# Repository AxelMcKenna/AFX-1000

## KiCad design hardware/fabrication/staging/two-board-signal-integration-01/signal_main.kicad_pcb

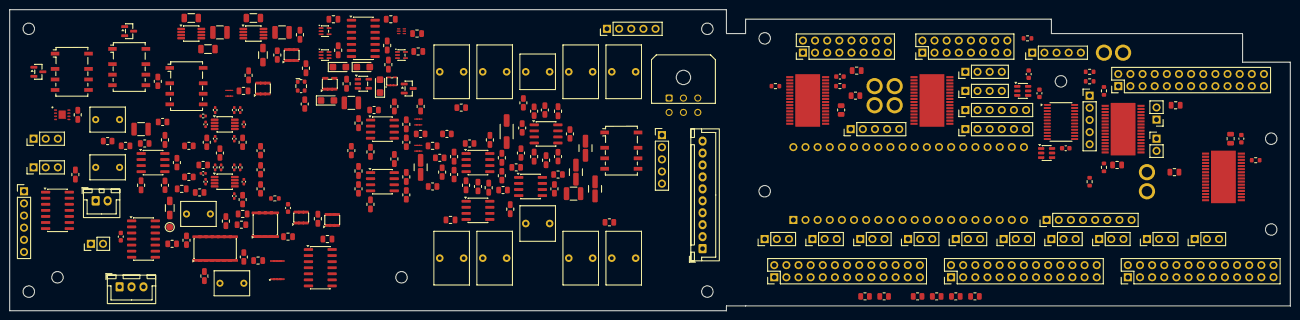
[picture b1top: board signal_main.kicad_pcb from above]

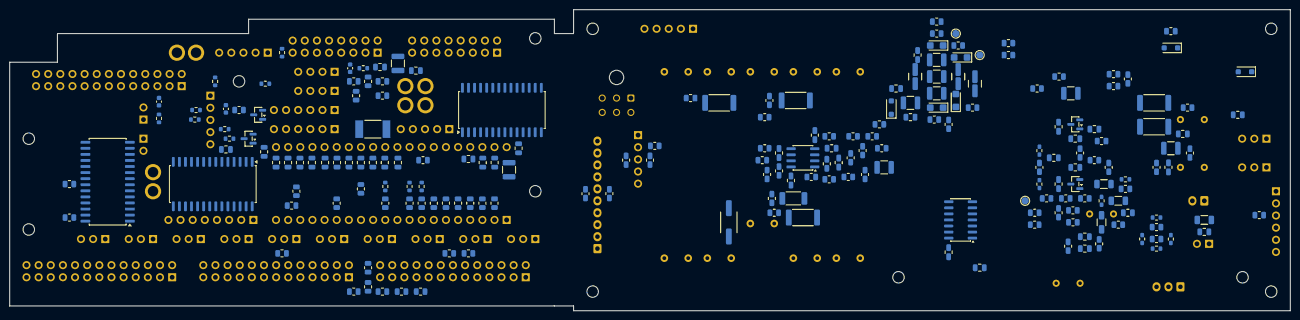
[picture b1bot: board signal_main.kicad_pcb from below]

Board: 8 copper layers, 268.0 x 63.0 mm, 477 parts (202 on the bottom side), 384 nets, no tracks yet.

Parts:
A_C101, A_C102, A_C115, A_C116: 1pF C0G +/-0.1pF; C_0402_1005Metric
A_C103, A_C117: 47pF C0G 5%; C_0805_2012Metric
A_C104, A_C105, A_C118, A_C119: 22pF C0G 5%; C_0805_2012Metric
A_C106, A_C120: 100nF 25V X7R; C_0805_2012Metric
A_C107, A_C121: 1uF 63V film 10%; C_Rect_L7.2mm_W5.0mm_P5.00mm
A_C108, A_C122: 10uF 16V X7R; C_1206_3216Metric
A_C109, A_C123: 47uF 25V X7S; C_1210_3225Metric
A_C110, A_C111, A_C124, A_C125: 47uF 6.3V X7S; C_1206_3216Metric
A_C112, A_C126: 2.2uF 16V X7R; C_0805_2012Metric
A_C113, A_C114, A_C127, A_C128: 100nF 16V X7R; C_0402_1005Metric
A_C129, A_C130, A_C131, A_C132, A_C220, A_C221, A_C222, A_C223, A_C224, A_C225, A_C226, A_C228, A_C229, A_C311, A_C312, A_C313, A_C314, A_C315, A_C316, A_C317, A_C318, A_C323, A_C324, A_C405, A_C406, A_C505, A_C506, A_C507, A_C508: 100nF 50V X7R; C_0805_2012Metric
A_C133, A_C134: 10uF 50V X7R; C_1206_3216Metric
A_C135, A_C136: 100nF 16V X7R; C_0603_1608Metric
A_C201, A_C202, A_C205: 1uF 10V X7R 10%; C_0805_2012Metric
A_C203, A_C210, A_C212, A_C214: 100nF 50V C0G 5%; C_1210_3225Metric
A_C204, A_C206, A_C207, A_C208, A_C209, A_C211, A_C213, A_C215: 1uF 10V tantalum 10%; CP_EIA-3216-18_Kemet-A
A_C216, A_C218, A_C227: 2.2uF 25V X7R 10%; C_1210_3225Metric
A_C217, A_C219: 10uF 16V X7R 10%; C_1210_3225Metric
A_C230, A_C231, A_C232, A_C610, A_C611, A_C612: 100nF 16V X7R; C_0805_2012Metric
A_C301, A_C302, A_C306, A_C307: 510pF 50V C0G 2%; C_0805_2012Metric
A_C303, A_C308: 51pF 50V C0G 2%; C_0805_2012Metric
A_C304, A_C305, A_C309, A_C310: 1nF 50V C0G 1%; C_0805_2012Metric
A_C319, A_C320, A_C509, A_C510, A_C511, A_C512: 10uF 50V X7R; C_1210_3225Metric
A_C321, A_C322: 2.2uF film 63V 10%; C_Rect_L7.2mm_W7.2mm_P5.00mm_FKS2_FKP2_MKS2_MKP2
A_C401, A_C403: 1uF film 63V 10%; C_Rect_L7.2mm_W5.0mm_P5.00mm
A_C402, A_C404: 47pF 50V C0G 5%; C_0805_2012Metric
A_C407, A_C408: 10uF 50V X7R 10%; C_1210_3225Metric
A_C501, A_C502, A_C503, A_C504, A_C513, A_C514, A_C515, A_C516: 4.7uF film 63V 10%; C_Rect_L7.2mm_W11.0mm_P5.00mm_FKS2_FKP2_MKS2_MKP2
A_C601: 150pF C0G 5%; C_0805_2012Metric
A_C602, A_C603, A_C604, A_C605, A_C606: 100nF X7R; C_0805_2012Metric
A_C607: 1uF 16V X7R; C_0805_2012Metric
A_C608: 22uF 16V X7R; C_1206_3216Metric
A_C609: 1uF 16V X7R 10%; C_0805_2012Metric
A_D101, A_D102: BAT54S,215; SOT-23
A_D601, A_D602, A_D603: SMF9.0A; D_SOD-123F
A_H1, A_H2, A_H3, A_H4: M2_CLEARANCE; M2_Clearance
A_H5, A_H6: M2_SHARED_SUPPORT; M2_Clearance
A_J203, A_J603: Conn_01x05; PinHeader_1x05_P2.54mm_Vertical
A_J402: B10B-XH-A(LF)(SN); JST_XH_B10B-XH-A_1x10_P2.50mm_Vertical
A_J403: B3B-XH-A(LF)(SN); JST_XH_B3B-XH-A_1x03_P2.50mm_Vertical
A_J602: Conn_01x06; PinHeader_1x06_P2.54mm_Vertical
A_J606: Conn_01x02; PinHeader_1x02_P2.54mm_Vertical
A_J607, A_J608: Conn_01x03; PinHeader_1x03_P2.54mm_Vertical
A_J701: 43045-0600; Molex_Micro-Fit_3.0_43045-0600_2x03_P3.00mm_Horizontal
A_J702: B2B-XH-A(LF)(SN); JST_XH_B2B-XH-A_1x02_P2.50mm_Vertical
A_K401, A_K503, A_K601, A_K602: G6K-2F-Y DC5; Relay_DPDT_Omron_G6K-2F-Y
A_Q601, A_Q602, A_Q603: AO3400A; SOT-23
A_R101, A_R102, A_R117, A_R118: 2.49k 0.05%; R_0402_1005Metric
A_R103, A_R104, A_R119, A_R120: 1.21k 0.05%; R_0402_1005Metric
A_R105, A_R106, A_R121, A_R122: 3.3R 1%; R_0805_2012Metric
A_R107, A_R123: 1M 1%; R_0805_2012Metric
A_R108, A_R109, A_R124, A_R125: 100k 0.01%; R_0805_2012Metric
A_R110, A_R111, A_R126, A_R127, A_R212: 10k 0.1%; R_0805_2012Metric
A_R112, A_R128: 10M 1%; R_0805_2012Metric
A_R113, A_R129, A_R203, A_R204, A_R601, A_R606: 10k 1%; R_0805_2012Metric
A_R114, A_R130, A_R205, A_R206, A_R603, A_R604, A_R605, A_R607, A_R615: 47k 1%; R_0805_2012Metric
A_R115, A_R131: 68k 1%; R_0805_2012Metric
A_R116, A_R132: 0.1R 1%; R_0805_2012Metric
A_R133: 1k 1%; R_0805_2012Metric
A_R134, A_R136: 100k 0.01%; R_0603_1608Metric
A_R135, A_R137, A_R139, A_R141: 10k 0.01%; R_0603_1608Metric
A_R138: 161k 0.01%; R_0805_2012Metric
A_R140: 240k 0.01%; R_0805_2012Metric
A_R142, A_R143: 10k 1%; R_0603_1608Metric
A_R144: 100k 1%; R_0603_1608Metric
A_R201, A_R202: 2k 1%; R_0805_2012Metric
A_R207, A_R208, A_R209, A_R210, A_R517, A_R518, A_R602, A_R617, A_R618: 100k 1%; R_0805_2012Metric
A_R211: 27.7k 0.1%; R_0805_2012Metric
A_R213, A_R214, A_R215, A_R216: 33 1%; R_0805_2012Metric
A_R301, A_R302, A_R313, A_R314: 1.8k 0.1%; R_0805_2012Metric
A_R303, A_R304, A_R315, A_R316: 4.3 1%; R_0805_2012Metric
A_R305, A_R306, A_R317, A_R318: 100k 0.1%; R_0805_2012Metric
A_R307, A_R319: 1.2M 0.1%; R_0805_2012Metric
A_R308, A_R309, A_R310, A_R311, A_R320, A_R321, A_R322, A_R323: 499 0.01%; R_0805_2012Metric
A_R312, A_R324, A_R407, A_R414: 33.2 0.1%; R_0805_2012Metric
A_R325, A_R326, A_R401, A_R408: 33.2k 0.1%; R_0805_2012Metric
A_R327, A_R328: 2.74k 0.1% 0.5W; R_2010_5025Metric
A_R402, A_R409: 13.7k 0.1%; R_0805_2012Metric
A_R403, A_R410: 4.99k 0.1% 1W; R_2512_6332Metric
A_R404, A_R411: 68k 0.1%; R_0805_2012Metric
A_R405, A_R412: 365 0.1%; R_0805_2012Metric
A_R406, A_R413, A_R502, A_R506: 1k 0.1%; R_0805_2012Metric
A_R501, A_R505: 5.23k 0.1%; R_0805_2012Metric
A_R503, A_R507, A_R511, A_R515: 100 1% 1W; R_2512_6332Metric
A_R504, A_R508, A_R512, A_R516: 20k 1%; R_0805_2012Metric
A_R509, A_R513: 1.21k 0.1%; R_0805_2012Metric
A_R510, A_R514: 2k 0.1%; R_0805_2012Metric
A_R608, A_R610, A_R612: 4.7k 1%; R_0805_2012Metric
A_R609, A_R611, A_R613: 270k 1%; R_0805_2012Metric
A_R614: 383k 0.1% 25ppm; R_0805_2012Metric
A_R616: 147k 1%; R_0805_2012Metric
A_TP401: TEST_ONLY_ADC_DRV_ENABLE; TestPoint_Pad_D1.5mm
A_TP402: TEST_ONLY_CHIP_EN; TestPoint_Pad_D1.5mm
A_TP403: TEST_ONLY_PD_GATED; TestPoint_Pad_D1.5mm
A_TP404: TEST_ONLY_AGND; TestPoint_Pad_D1.5mm
A_U101, A_U102: THS4551IDGKR; VSSOP-8_3x3mm_P0.65mm
A_U103, A_U305, A_U401: OPA1656ID; SOIC-8_3.9x4.9mm_P1.27mm
A_U104: OPA4192ID; SOIC-14_3.9x8.7mm_P1.27mm
A_U105, A_U106: LM7705MM/NOPB; VSSOP-8_3x3mm_P0.65mm
A_U107: TLV9024DR; SOIC-14_3.9x8.7mm_P1.27mm
A_U108, A_U605: TPS3808G50DBVR; SOT-23-6
A_U202: TPS7A2033PDBVR; SOT-23-5
A_U203: TPS7A2045PDBVR; SOT-23-5
A_U204, A_U205, A_U208: TPS389033DSET; TI_DSE0006A_TPS3890
A_U206: TPS389001DSET; TI_DSE0006A_TPS3890
A_U207, A_U602, A_U606: SN74HCS08DR; SOIC-14_3.9x8.7mm_P1.27mm
A_U209, A_U212: SN74LVC1G08DCKR; SOT-353_SC-70-5
A_U210: SN74LVC2G17DCKR; SOT-363_SC-70-6
A_U211: SN74LVC1G17DCKR; SOT-353_SC-70-5
A_U301, A_U302, A_U303, A_U304, A_U502: OPA1612AID; SOIC-8_3.9x4.9mm_P1.27mm
A_U501: OPA2992D; SOIC-8_3.9x4.9mm_P1.27mm
A_U601: TPS3431SDRBR; TI_DRB0008A_TPS3431
A_U603: SN74LVC1G74DCTR; TI_DCT0008A_SN74LVC1G74
A_U604: TPS3808G33DBVR; SOT-23-6
A_U607: LTC6994HS6-1#TRMPBF; TSOT-23-6
A_U608: SN74HCS86DR; SOIC-14_3.9x8.7mm_P1.27mm
A_Y201: ECS-2520MVLC-245.7-BN-TR; Oscillator_SMD_ECS_2520MV-xxx-xx-4Pin_2.5x2.0mm
D_C1001, D_C3013: 22uF 25V X7R; C_1210_3225Metric
D_C1002, D_C1004, D_C1006, D_C1011, D_C1012, D_C1013, D_C1014, D_C1015, D_C1016, D_C1017, D_C1018, D_C1019, D_C1020, D_C2001, D_C2002, D_C2003: 100nF 16V X7R; C_0805_2012Metric
D_C1003, D_C2004: 1uF 16V X7R; C_0805_2012Metric
D_C1005, D_C3002, D_C3004, D_C3006, D_C3008, D_C3014: 4.7uF 16V X7R; C_0805_2012Metric
D_C3001, D_C3003, D_C3005, D_C3007, D_C3009, D_C3010, D_C3011, D_C3012: 100nF 16V X7R; C_0603_1608Metric
D_H1, D_H2, D_H3, D_H4, D_H5: M2_CLEARANCE; M2_Clearance
D_J1001, D_J1013, D_J1014, D_J1015: Alpha6715_AWG18_DIRECT_SOLDER_PROPOSAL; AWG18_Solder_2x1_P4mm_D2p2
D_J1003, D_J1006: Header6; PinHeader_1x06_P2.54mm_Vertical
D_J1004, D_J1005, D_J2003: Header5; PinHeader_1x05_P2.54mm_Vertical
D_J1007, D_J1008: Header2; PinHeader_1x02_P2.54mm_Vertical
D_J1009, D_J1010: Header4; PinHeader_1x04_P2.54mm_Vertical
D_J1012: Header8; PinHeader_1x08_P2.54mm_Vertical
D_J1020, D_J1021, D_J1022, D_J1023, D_J1024, D_J1025, D_J1026, D_J1027, D_J1028, D_J1029: Header3; PinHeader_1x03_P2.54mm_Vertical
D_J2001, D_J2002: Header16; PinHeader_2x08_P2.54mm_Vertical
D_J3002, D_J3003, D_J3004, D_J3005: Header26; PinHeader_2x13_P2.54mm_Vertical
D_Q3001, D_Q3002: AO3400A; SOT-23
D_R1001: 0.47R 1% WSLT2512R4700FEA P70=0.815W; WSLT2512_R_2512_Manufacturer
D_R1002: 10k 1%; R_0805_2012Metric
D_R1003, D_R1004, D_R1005, D_R1006, D_R2001: 100k 1%; R_0805_2012Metric
D_R1010, D_R1011, D_R1012, D_R1013, D_R1014, D_R1015, D_R1016, D_R1017, D_R1018, D_R1019, D_R1020: 33R 1%; R_0805_2012Metric
D_R1031, D_R1032, D_R1033, D_R1034, D_R1035, D_R1036, D_R1037, D_R1038, D_R1039, D_R1040: 1k 1%; R_0805_2012Metric
D_R1041, D_R1042, D_R1043, D_R1044, D_R1045, D_R1046, D_R1047, D_R1048, D_R1049, D_R1050: 1M 1%; R_0805_2012Metric
D_R2002: 47k 1%; R_0805_2012Metric
D_R2003: 270k 1%; R_0805_2012Metric
D_R3001, D_R3002, D_R3003, D_R3004: 16.5k 1%; R_0603_1608Metric
D_R3005: 47k 1%; R_0603_1608Metric
D_R3006, D_R3007, D_R3010, D_R3011: 10k 1%; R_0603_1608Metric
D_R3008, D_R3009, D_R3012, D_R3013, D_R3014, D_R3019, D_R3020, D_R3021: 100k 1%; R_0603_1608Metric
D_R3015, D_R3016, D_R3017, D_R3018: 33R 1%; R_0603_1608Metric
D_U1001: DaisySeed3; Seed3_Socket40
D_U2001, D_U2002, D_U2003: MCP23017-E/SO; SOIC-28W_7.5x17.9mm_P1.27mm
D_U3001, D_U3002, D_U3003, D_U3004: TLC5947DAPR; TLC5947_DAP0032C
D_U3005: SN74LVC8T245PWR; TSSOP-24_4.4x7.8mm_P0.65mm
D_U3006: TPS3808G33DBVR; SOT-23-6
D_U3007: TPS3808G50DBVR; SOT-23-6

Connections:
audio_main::5V_DIG: A_C608.1, A_J702.1, A_K401.1, A_K503.1, A_K601.1, A_K602.1, A_U605.5
audio_main::/ADC/BIAS_SHIFT_L: A_R134.2, A_R135.1, A_U107.4, A_U107.7
audio_main::/ADC/BIAS_SHIFT_R: A_R136.2, A_R137.1, A_U107.8, A_U107.11
audio_main::/ADC/BUF_L: A_R101.1, A_U103.1, A_U103.2
audio_main::/ADC/BUF_R: A_R117.1, A_U103.6, A_U103.7
audio_main::/ADC/CM_DRIVE_L: A_C107.1, A_R112.1, A_R113.1, A_U104.7
audio_main::/ADC/CM_DRIVE_R: A_C121.1, A_R128.1, A_R129.1, A_U104.14
audio_main::/ADC/CM_SENSE_L: A_C107.2, A_R110.2, A_R111.2, A_R112.2, A_U104.6
audio_main::/ADC/CM_SENSE_R: A_C121.2, A_R126.2, A_R127.2, A_R128.2, A_U104.13
audio_main::/ADC/DRV_LN: A_C101.1, A_R106.1, A_U101.5
audio_main::/ADC/DRV_LP: A_C102.1, A_R105.1, A_U101.4
audio_main::/ADC/DRV_RN: A_C115.1, A_R122.1, A_U102.5
audio_main::/ADC/DRV_RP: A_C116.1, A_R121.1, A_U102.4
audio_main::/ADC/FB_N_L: A_C102.2, A_R102.2, A_R104.2, A_U101.1
audio_main::/ADC/FB_N_R: A_C116.2, A_R118.2, A_R120.2, A_U102.1
audio_main::/ADC/FB_P_L: A_C101.2, A_R101.2, A_R103.2, A_U101.8
audio_main::/ADC/FB_P_R: A_C115.2, A_R117.2, A_R119.2, A_U102.8
audio_main::/ADC/FLY_N_L: A_C108.2, A_U105.8
audio_main::/ADC/FLY_N_R: A_C122.2, A_U106.8
audio_main::/ADC/FLY_P_L: A_C108.1, A_U105.1
audio_main::/ADC/FLY_P_R: A_C122.1, A_U106.1
audio_main::/ADC/NBIAS_L: A_C111.1, A_C114.1, A_J403.2, A_R115.2, A_R116.2, A_R135.2, A_U101.6
audio_main::/ADC/NBIAS_R: A_C125.1, A_C128.1, A_J403.3, A_R131.2, A_R132.2, A_R137.2, A_U102.6
audio_main::/ADC/NPUMP_L: A_C110.1, A_R116.1, A_U105.6
audio_main::/ADC/NPUMP_R: A_C124.1, A_R132.1, A_U106.6
audio_main::/ADC/PD_GATED: A_R114.1, A_R130.1, A_R143.2, A_R144.1, A_TP403.1, A_U108.1
audio_main::/ADC/PD_L: A_R114.2, A_R115.1, A_U101.7
audio_main::/ADC/PD_R: A_R130.2, A_R131.1, A_U102.7
audio_main::/ADC/REF_DIV_L: A_C106.1, A_R108.2, A_R109.1, A_U104.3
audio_main::/ADC/REF_DIV_R: A_C120.1, A_R124.2, A_R125.1, A_U104.10
audio_main::/ADC/REF_HALF_L: A_U104.1, A_U104.2, A_U104.5
audio_main::/ADC/REF_HALF_R: A_U104.8, A_U104.9, A_U104.12
audio_main::/ADC/RES_L: A_C109.1, A_U105.7
audio_main::/ADC/RES_R: A_C123.1, A_U106.7
audio_main::/ADC/THRESH_LOWER: A_R140.2, A_R141.1, A_U107.6, A_U107.10
audio_main::/ADC/THRESH_UPPER: A_R138.2, A_R139.1, A_U107.5, A_U107.9
audio_main::/ADC/VOCM_L: A_D101.3, A_R113.2, A_U101.2
audio_main::/ADC/VOCM_R: A_D102.3, A_R129.2, A_U102.2
audio_main::/BYPASS/ARMED: A_J602.5, A_U602.9, A_U603.3
audio_main::/BYPASS/BYPASS_GATE: A_Q601.1, A_R608.2, A_R609.1
audio_main::/BYPASS/BYPASS_LOW: A_D601.1, A_K601.8, A_Q601.3
audio_main::/BYPASS/BYPASS_SENSE: A_J602.6, A_J603.5, A_R606.2
audio_main::/BYPASS/CLEAR_N: A_U603.6, A_U606.5, A_U606.8
audio_main::/BYPASS/COIL_ENABLE: A_U602.8, A_U606.4
audio_main::/BYPASS/CWD: A_C601.1, A_U601.2
audio_main::/BYPASS/FINAL_ENABLE: A_R608.1, A_U606.6
audio_main::/BYPASS/GAIN_DELAY: A_C609.1, A_R615.2, A_U608.2
audio_main::/BYPASS/GAIN_EDGE: A_U608.3, A_U608.4
audio_main::/BYPASS/GAIN_GATE: A_Q602.1, A_R610.2, A_R611.1
audio_main::/BYPASS/GAIN_REQ: A_J602.4, A_R607.1, A_R610.1, A_R615.1, A_U608.1
audio_main::/BYPASS/GAIN_STABLE: A_U606.13, A_U608.6
audio_main::/BYPASS/HEARTBEAT: A_J602.2, A_R602.1, A_U601.6
audio_main::/BYPASS/INPUT_ENABLE: A_R612.1, A_U602.3, A_U602.4, A_U606.12
audio_main::/BYPASS/INPUT_GATE: A_Q603.1, A_R612.2, A_R613.1
audio_main::/BYPASS/INPUT_LOW: A_D603.1, A_K602.8, A_Q603.3
audio_main::/BYPASS/INPUT_READY: A_J606.2, A_U606.3, A_U606.9
audio_main::/BYPASS/IN_L: A_J607.1, A_K601.2, A_K602.4
audio_main::/BYPASS/IN_R: A_J607.3, A_K601.7, A_K602.5
audio_main::/BYPASS/LOCAL_OK: A_R601.2, A_U601.7, A_U601.8, A_U602.1, A_U604.1, A_U605.1
audio_main::/BYPASS/MCU_PERMIT: A_J602.3, A_R603.1, A_U602.12, A_U602.13
audio_main::/BYPASS/OUT_L: A_J608.1, A_K601.3
audio_main::/BYPASS/OUT_R: A_J608.3, A_K601.6
audio_main::/BYPASS/PERMIT_CLEAN: A_U602.10, A_U602.11, A_U603.1
audio_main::/BYPASS/PROCESS_HEALTH: A_U602.6, A_U606.10
audio_main::/BYPASS/PROCESS_OK: A_J603.2, A_R604.1, A_U602.5
audio_main::/BYPASS/STARTUP_CT: A_R618.2, A_U604.4
audio_main::/BYPASS/TIMER_DIV: A_R616.2, A_R617.1, A_U607.4
audio_main::/BYPASS/TIMER_ENABLE: A_U606.1, A_U606.11, A_U607.1
audio_main::/BYPASS/TIMER_INPUT_OK: A_U606.2, A_U607.6
audio_main::/BYPASS/TIMER_SET: A_R614.1, A_U607.3
audio_main::/CODEC/A3V3: A_C205.1, A_C217.1, A_C229.1, A_U202.5, A_U205.1
audio_main::/CODEC/A4V5: A_C207.1, A_C219.1, A_R211.1, A_U203.5
audio_main::/CODEC/ADC_BIAS_IO: A_U211.4, A_U212.2
audio_main::/CODEC/ADC_DATA: A_J203.4, A_R216.2
audio_main::/CODEC/BCLK: A_J203.2, A_R214.2
audio_main::/CODEC/CHIP_REQUEST: A_U207.6, A_U210.1
audio_main::/CODEC/CLK_VALID: A_R207.1, A_U207.9
audio_main::/CODEC/CODEC_FLAGS: A_U207.8, A_U207.13
audio_main::/CODEC/CODEC_PGOOD: A_J402.9, A_R203.1, A_U204.6, A_U205.6, A_U206.6, A_U207.1
audio_main::/CODEC/CODEC_RUN: A_J402.5, A_R205.1, A_U207.5
audio_main::/CODEC/CT_SETTLE: A_C227.1, A_U208.5
audio_main::/CODEC/DRIVER_SETTLE_READY: A_U208.3, A_U209.1, A_U212.4
audio_main::/CODEC/MCLK_SRC: A_R213.1, A_Y201.3
audio_main::/CODEC/PRE_ANALOG_OK: A_J402.8, A_R206.1, A_U207.2
audio_main::/CODEC/RAMP_DONE: A_R208.1, A_U207.10
audio_main::/CODEC/REF_DAC_BUF: A_C203.1, A_C204.1
audio_main::/CODEC/REF_PLL: A_C210.1, A_C211.1
audio_main::/CODEC/SCL: A_J402.3, A_R201.1
audio_main::/CODEC/SDA: A_J402.4, A_R202.1
audio_main::/CODEC/SENSE_4V5: A_R211.2, A_R212.1, A_U206.1
audio_main::/CODEC/SETTLE_ENABLE: A_U207.11, A_U210.3, A_U212.1
audio_main::/CODEC/SUPPLY_OK: A_U207.3, A_U207.4
audio_main::/CODEC/TIMER_OK: A_R204.1, A_U208.6, A_U209.2
audio_main::/CODEC/WS: A_J203.3, A_R215.2
audio_main::/DAC/BIAS_N_L: A_R304.2, A_U301.5
audio_main::/DAC/BIAS_N_R: A_R316.2, A_U302.5
audio_main::/DAC/BIAS_P_L: A_R303.2, A_U301.3
audio_main::/DAC/BIAS_P_R: A_R315.2, A_U302.3
audio_main::/DAC/BUF_IN_L: A_R327.2, A_U305.3
audio_main::/DAC/BUF_IN_R: A_R328.2, A_U305.5
audio_main::/DAC/BUF_OUT_L: A_R312.1, A_U305.1, A_U305.2
audio_main::/DAC/BUF_OUT_R: A_R324.1, A_U305.6, A_U305.7
audio_main::/DAC/CM_DRV_L: A_C303.2, A_R303.1, A_R304.1, A_R307.2, A_U303.1
audio_main::/DAC/CM_DRV_R: A_C308.2, A_R315.1, A_R316.1, A_R319.2, A_U303.7
audio_main::/DAC/CM_SUM_L: A_C303.1, A_R305.2, A_R306.2, A_R307.1, A_U303.2
audio_main::/DAC/CM_SUM_R: A_C308.1, A_R317.2, A_R318.2, A_R319.1, A_U303.6
audio_main::/DAC/HP_NODE_L: A_C321.2, A_R325.1, A_R327.1
audio_main::/DAC/HP_NODE_R: A_C322.2, A_R326.1, A_R328.1
audio_main::/DAC/IV_N_L: A_C302.2, A_R302.2, A_R306.1, A_R309.1, A_U301.7
audio_main::/DAC/IV_N_R: A_C307.2, A_R314.2, A_R318.1, A_R321.1, A_U302.7
audio_main::/DAC/IV_P_L: A_C301.2, A_R301.2, A_R305.1, A_R308.1, A_U301.1
audio_main::/DAC/IV_P_R: A_C306.2, A_R313.2, A_R317.1, A_R320.1, A_U302.1
audio_main::/DAC/RX_NEG_L: A_C304.1, A_R308.2, A_R310.1, A_U304.2
audio_main::/DAC/RX_NEG_R: A_C309.1, A_R320.2, A_R322.1, A_U304.6
audio_main::/DAC/RX_OUT_L: A_C304.2, A_C321.1, A_R310.2, A_U304.1
audio_main::/DAC/RX_OUT_R: A_C309.2, A_C322.1, A_R322.2, A_U304.7
audio_main::/DAC/RX_POS_L: A_C305.1, A_R309.2, A_R311.1, A_U304.3
audio_main::/DAC/RX_POS_R: A_C310.1, A_R321.2, A_R323.1, A_U304.5
audio_main::/INPUT/ATTN_L: A_K401.2, A_R401.2, A_R402.1
audio_main::/INPUT/ATTN_R: A_K401.7, A_R408.2, A_R409.1
audio_main::/INPUT/BUF_IN_L: A_C401.2, A_C402.1, A_R404.1, A_U401.3
audio_main::/INPUT/BUF_IN_R: A_C403.2, A_C404.1, A_R411.1, A_U401.5
audio_main::/INPUT/BUF_OUT_L: A_R405.2, A_R407.1, A_U401.1
audio_main::/INPUT/BUF_OUT_R: A_R412.2, A_R414.1, A_U401.7
audio_main::/INPUT/GAIN_FB_L: A_R405.1, A_R406.1, A_U401.2
audio_main::/INPUT/GAIN_FB_R: A_R412.1, A_R413.1, A_U401.6
audio_main::/INPUT/HP_SRC_L: A_C401.1, A_R403.2
audio_main::/INPUT/HP_SRC_R: A_C403.1, A_R410.2
audio_main::/INPUT/RANGE_L: A_K401.3, A_R403.1
audio_main::/INPUT/RANGE_R: A_K401.6, A_R410.1
audio_main::/OUTPUT/M_AC_L: A_C501.2, A_C513.2, A_K503.2, A_R504.1
audio_main::/OUTPUT/M_AC_R: A_C502.2, A_C514.2, A_K503.7, A_R508.1
audio_main::/OUTPUT/M_DRV_L: A_R501.2, A_R503.1, A_U501.1
audio_main::/OUTPUT/M_DRV_R: A_R505.2, A_R507.1, A_U501.7
audio_main::/OUTPUT/M_FB_L: A_R501.1, A_R502.1, A_U501.2
audio_main::/OUTPUT/M_FB_R: A_R505.1, A_R506.1, A_U501.6
audio_main::/OUTPUT/M_SER_L: A_C501.1, A_C513.1, A_R503.2
audio_main::/OUTPUT/M_SER_R: A_C502.1, A_C514.1, A_R507.2
audio_main::/OUTPUT/S_AC_L: A_C503.2, A_C515.2, A_K503.4, A_R512.1
audio_main::/OUTPUT/S_AC_R: A_C504.2, A_C516.2, A_K503.5, A_R516.1
audio_main::/OUTPUT/S_DRV_L: A_R509.2, A_R511.1, A_U502.1
audio_main::/OUTPUT/S_DRV_R: A_R513.2, A_R515.1, A_U502.7
audio_main::/OUTPUT/S_FB_L: A_R509.1, A_R510.1, A_U502.2
audio_main::/OUTPUT/S_FB_R: A_R513.1, A_R514.1, A_U502.6
audio_main::/OUTPUT/S_SER_L: A_C503.1, A_C515.1, A_R511.2
audio_main::/OUTPUT/S_SER_R: A_C504.1, A_C516.1, A_R515.2
audio_main::ADC_BIAS_WINDOW_OK: A_R142.2, A_U107.1, A_U107.2, A_U107.13, A_U107.14, A_U108.3, A_U211.2
audio_main::ADC_DRV_ENABLE: A_R143.1, A_TP401.1, A_U210.4
audio_main::ADC_LN: A_C103.2, A_C105.1, A_R103.1, A_R106.2, A_R111.1
audio_main::ADC_LP: A_C103.1, A_C104.1, A_R104.1, A_R105.2, A_R110.1
audio_main::ADC_RN: A_C117.2, A_C119.1, A_R119.1, A_R122.2, A_R127.1
audio_main::ADC_RP: A_C117.1, A_C118.1, A_R120.1, A_R121.2, A_R126.1
audio_main::AGND: A_C104.2, A_C105.2, A_C106.2, A_C109.2, A_C110.2, A_C111.2, A_C112.2, A_C113.2, A_C114.2, A_C118.2, A_C119.2, A_C120.2, A_C123.2, A_C124.2, A_C125.2, A_C126.2, A_C127.2, A_C128.2, A_C129.2, A_C130.2, A_C131.2, A_C132.2, A_C133.2, A_C134.2, A_C135.2, A_C136.2, A_C201.2, A_C202.2, A_C203.2, A_C204.2, A_C205.2, A_C206.2, A_C207.2, A_C208.2, A_C209.2, A_C210.2, A_C211.2, A_C212.2, A_C213.2, A_C214.2, A_C215.2, A_C216.2, A_C217.2, A_C218.2, A_C219.2, A_C220.2, A_C221.2, A_C222.2, A_C223.2, A_C224.2, A_C225.2, A_C226.2, A_C227.2, A_C228.2, A_C229.2, A_C230.2, A_C231.2, A_C232.2, A_C305.2, A_C310.2, A_C311.2, A_C312.2, A_C313.2, A_C314.2, A_C315.2, A_C316.2, A_C317.2, A_C318.2, A_C319.2, A_C320.2, A_C323.2, A_C324.2, A_C402.2, A_C404.2, A_C405.2, A_C406.2, A_C407.2, A_C408.2, A_C505.2, A_C506.2, A_C507.2, A_C508.2, A_C509.2, A_C510.2, A_C511.2, A_C512.2, A_C601.2, A_C602.2, A_C603.2, A_C604.2, A_C605.2, A_C606.2, A_C607.2, A_C608.2, A_C609.2, A_C610.2, A_C611.2, A_C612.2, A_D101.1, A_D102.1, A_D601.2, A_D602.2, A_D603.2, A_J203.1, A_J402.1, A_J402.7, A_J403.1, A_J602.1, A_J603.4, A_J606.1, A_J607.2, A_J608.2, A_J701.2, A_J702.2, A_Q601.2, A_Q602.2, A_Q603.2, A_R102.1, A_R107.2, A_R109.2, A_R118.1, A_R123.2, A_R125.2, A_R133.2, A_R139.2, A_R141.2, A_R144.2, A_R205.2, A_R206.2, A_R207.2, A_R208.2, A_R209.2, A_R210.2, A_R212.2, A_R311.2, A_R323.2, A_R325.2, A_R326.2, A_R402.2, A_R404.2, A_R406.2, A_R409.2, A_R411.2, A_R413.2, A_R502.2, A_R504.2, A_R506.2, A_R508.2, A_R510.2, A_R512.2, A_R514.2, A_R516.2, A_R517.2, A_R518.2, A_R602.2, A_R603.2, A_R604.2, A_R605.2, A_R607.2, A_R609.2, A_R611.2, A_R613.2, A_R614.2, A_R617.2, A_TP404.1, A_U105.2, A_U105.3, A_U105.5, A_U106.2, A_U106.3, A_U106.5, A_U107.12, A_U108.2, A_U202.2, A_U203.2, A_U204.2, A_U205.2, A_U206.2, A_U207.7, A_U208.2, A_U209.3, A_U210.2, A_U211.3, A_U212.3, A_U303.3, A_U303.5, A_U601.4, A_U601.9, A_U602.7, A_U603.4, A_U604.2, A_U605.2, A_U606.7, A_U607.2, A_U608.7, A_U608.9, A_U608.10, A_U608.12, A_U608.13, A_Y201.2
audio_main::ANALOG_OK: A_J402.6, A_J402.10, A_J603.3, A_R210.1, A_R605.1, A_U209.4, A_U602.2
audio_main::CHIP_EN: A_R209.1, A_TP402.1, A_U207.12, A_U210.6
audio_main::DAC_LN: A_C302.1, A_R302.1, A_U301.6
audio_main::DAC_LP: A_C301.1, A_R301.1, A_U301.2
audio_main::DAC_RN: A_C307.1, A_R314.1, A_U302.6
audio_main::DAC_RP: A_C306.1, A_R313.1, A_U302.2
audio_main::GAIN_LOW: A_D602.1, A_K401.8, A_K503.8, A_Q602.3
audio_main::N12: A_C130.1, A_C132.1, A_C134.1, A_C312.1, A_C314.1, A_C316.1, A_C318.1, A_C320.1, A_C324.1, A_C406.1, A_C408.1, A_C508.1, A_C512.1, A_J701.5, A_U103.4, A_U104.11, A_U301.4, A_U302.4, A_U303.4, A_U304.4, A_U305.4, A_U401.4, A_U502.4
audio_main::N19: A_C506.1, A_C510.1, A_J701.3, A_U501.4
audio_main::P12: A_C129.1, A_C131.1, A_C133.1, A_C311.1, A_C313.1, A_C315.1, A_C317.1, A_C319.1, A_C323.1, A_C405.1, A_C407.1, A_C507.1, A_C511.1, A_J701.4, A_U103.8, A_U104.4, A_U301.8, A_U302.8, A_U303.8, A_U304.8, A_U305.8, A_U401.8, A_U502.8
audio_main::P19: A_C505.1, A_C509.1, A_J701.1, A_U501.8
audio_main::PRE_OUT_L: A_R107.1, A_R407.2, A_U103.3
audio_main::PRE_OUT_R: A_R123.1, A_R414.2, A_U103.5
audio_main::PROC_IN_L: A_K401.4, A_K602.3, A_R401.1
audio_main::PROC_IN_R: A_K401.5, A_K602.6, A_R408.1
audio_main::PROC_OUT_L: A_K503.3, A_K601.4
audio_main::PROC_OUT_R: A_K503.6, A_K601.5
audio_main::RECV_L: A_R312.2, A_R517.1, A_U501.3, A_U502.3
audio_main::RECV_R: A_R324.2, A_R518.1, A_U501.5, A_U502.5
audio_main::REF_ADC1: A_C212.1, A_C213.1, A_R108.1
audio_main::REF_ADC2: A_C214.1, A_C215.1, A_R124.1
audio_main::V3V3_IO: A_C201.1, A_C220.1, A_C221.1, A_C222.1, A_C223.1, A_C224.1, A_C225.1, A_C226.1, A_C228.1, A_C230.1, A_C231.1, A_C232.1, A_C602.1, A_C603.1, A_C604.1, A_C605.1, A_C606.1, A_C607.1, A_C610.1, A_C611.1, A_C612.1, A_J402.2, A_J603.1, A_R201.2, A_R202.2, A_R203.2, A_R204.2, A_R601.1, A_R606.1, A_R616.1, A_R618.1, A_U204.1, A_U204.3, A_U204.4, A_U205.3, A_U205.4, A_U206.3, A_U206.4, A_U207.14, A_U208.1, A_U208.4, A_U209.5, A_U210.5, A_U211.5, A_U212.5, A_U601.1, A_U601.3, A_U601.5, A_U602.14, A_U603.2, A_U603.7, A_U603.8, A_U604.3, A_U604.5, A_U604.6, A_U605.3, A_U605.6, A_U606.14, A_U607.5, A_U608.5, A_U608.14, A_Y201.1, A_Y201.4
audio_main::V5_REG: A_C112.1, A_C113.1, A_C126.1, A_C127.1, A_C135.1, A_C136.1, A_C216.1, A_C218.1, A_D101.2, A_D102.2, A_J701.6, A_R133.1, A_R134.1, A_R136.1, A_R138.1, A_R140.1, A_R142.1, A_U101.3, A_U102.3, A_U105.4, A_U106.4, A_U107.3, A_U108.5, A_U108.6, A_U202.1, A_U202.3, A_U203.1, A_U203.3
digital_core::5V_DIG: D_C3001.1, D_C3002.1, D_C3003.1, D_C3004.1, D_C3005.1, D_C3006.1, D_C3007.1, D_C3008.1, D_C3010.1, D_C3012.1, D_C3013.1, D_C3014.1, D_J1001.1, D_J1013.1, D_J1014.1, D_J1015.1, D_J3002.25, D_J3002.26, D_J3003.25, D_J3003.26, D_J3004.25, D_J3004.26, D_J3005.25, D_J3005.26, D_R1001.1, D_R3007.2, D_R3011.2, D_U3001.32, D_U3002.32, D_U3003.32, D_U3004.32, D_U3005.23, D_U3005.24, D_U3007.3, D_U3007.5, D_U3007.6
digital_core::/CONTROLS/CONTROL_00: D_J2001.13, D_U2001.21
digital_core::/CONTROLS/CONTROL_01: D_J2001.11, D_U2001.22
digital_core::/CONTROLS/CONTROL_02: D_J2001.9, D_U2001.23
digital_core::/CONTROLS/CONTROL_03: D_J2001.7, D_U2001.24
digital_core::/CONTROLS/CONTROL_04: D_J2001.5, D_U2001.25
digital_core::/CONTROLS/CONTROL_05: D_J2001.3, D_U2001.26
digital_core::/CONTROLS/CONTROL_06: D_J2001.1, D_U2001.27
digital_core::/CONTROLS/CONTROL_07: D_J2001.2, D_U2001.1
digital_core::/CONTROLS/CONTROL_08: D_J2001.4, D_U2001.2
digital_core::/CONTROLS/CONTROL_09: D_J2001.6, D_U2001.3
digital_core::/CONTROLS/CONTROL_10: D_J2001.8, D_U2001.4
digital_core::/CONTROLS/CONTROL_11: D_J2001.10, D_U2001.5
digital_core::/CONTROLS/CONTROL_12: D_J2001.12, D_U2001.6
digital_core::/CONTROLS/CONTROL_13: D_J2001.14, D_U2001.7
digital_core::/CONTROLS/CONTROL_14: D_J2002.13, D_U2002.21
digital_core::/CONTROLS/CONTROL_15: D_J2002.11, D_U2002.22
digital_core::/CONTROLS/CONTROL_16: D_J2002.9, D_U2002.23
digital_core::/CONTROLS/CONTROL_17: D_J2002.7, D_U2002.24
digital_core::/CONTROLS/CONTROL_18: D_J2002.5, D_U2002.25
digital_core::/CONTROLS/CONTROL_19: D_J2002.3, D_U2002.26
digital_core::/CONTROLS/CONTROL_20: D_J2002.1, D_U2002.27
digital_core::/CONTROLS/CONTROL_21: D_J2002.2, D_U2002.1
digital_core::/CONTROLS/CONTROL_22: D_J2002.4, D_U2002.2
digital_core::/CONTROLS/CONTROL_23: D_J2002.6, D_U2002.3
digital_core::/CONTROLS/CONTROL_24: D_J2002.8, D_U2002.4
digital_core::/CONTROLS/CONTROL_25: D_J2002.10, D_U2002.5
digital_core::/CONTROLS/CONTROL_26: D_J2002.12, D_U2002.6
digital_core::/CONTROLS/CONTROL_27: D_J2002.14, D_U2002.7
digital_core::/CONTROLS/CONTROL_28: D_J2003.2, D_U2003.1
digital_core::/CONTROLS/CONTROL_29: D_J2003.3, D_U2003.2
digital_core::/CONTROLS/CONTROL_30: D_J2003.4, D_U2003.3
digital_core::/CONTROLS/CONTROL_31: D_J2003.5, D_U2003.4
digital_core::/LED/BLANK_5V: D_R3011.1, D_R3018.2, D_U3001.2, D_U3002.2, D_U3003.2, D_U3004.2
digital_core::/LED/BLANK_5V_SRC: D_R3018.1, D_U3005.18
digital_core::/LED/CLOCK_5V: D_R3013.1, D_R3016.2, D_U3001.3, D_U3002.3, D_U3003.3, D_U3004.3
digital_core::/LED/CLOCK_5V_SRC: D_R3016.1, D_U3005.20
digital_core::/LED/DATA_5V: D_R3012.1, D_R3015.2, D_U3001.4
digital_core::/LED/DATA_5V_SRC: D_R3015.1, D_U3005.21
digital_core::/LED/ENABLE_MID: D_Q3001.2, D_Q3002.3
digital_core::/LED/IREF_0: D_R3001.1, D_U3001.31
digital_core::/LED/IREF_1: D_R3002.1, D_U3002.31
digital_core::/LED/IREF_2: D_R3003.1, D_U3003.31
digital_core::/LED/IREF_3: D_R3004.1, D_U3004.31
digital_core::/LED/LATCH_5V: D_R3014.1, D_R3017.2, D_U3001.30, D_U3002.30, D_U3003.30, D_U3004.30
digital_core::/LED/LATCH_5V_SRC: D_R3017.1, D_U3005.19
digital_core::/LED/LED_00: D_J3003.1, D_U3001.5
digital_core::/LED/LED_01: D_J3003.2, D_U3001.6
digital_core::/LED/LED_02: D_J3003.3, D_U3001.7
digital_core::/LED/LED_03: D_J3003.4, D_U3001.8
digital_core::/LED/LED_04: D_J3003.5, D_U3001.9
digital_core::/LED/LED_05: D_J3003.6, D_U3001.10
digital_core::/LED/LED_06: D_J3003.7, D_U3001.11
digital_core::/LED/LED_07: D_J3003.8, D_U3001.12
digital_core::/LED/LED_08: D_J3003.9, D_U3001.13
digital_core::/LED/LED_09: D_J3003.10, D_U3001.14
digital_core::/LED/LED_10: D_J3003.11, D_U3001.15
digital_core::/LED/LED_11: D_J3003.12, D_U3001.16
digital_core::/LED/LED_12: D_J3002.12, D_U3001.17
digital_core::/LED/LED_13: D_J3002.11, D_U3001.18
digital_core::/LED/LED_14: D_J3002.10, D_U3001.19
digital_core::/LED/LED_15: D_J3002.9, D_U3001.20
digital_core::/LED/LED_16: D_J3002.8, D_U3001.21
digital_core::/LED/LED_17: D_J3002.7, D_U3001.22
digital_core::/LED/LED_18: D_J3002.6, D_U3001.23
digital_core::/LED/LED_19: D_J3002.5, D_U3001.24
digital_core::/LED/LED_20: D_J3002.4, D_U3001.25
digital_core::/LED/LED_21: D_J3002.3, D_U3001.26
digital_core::/LED/LED_22: D_J3002.2, D_U3001.27
digital_core::/LED/LED_23: D_J3002.1, D_U3001.28
digital_core::/LED/LED_24: D_J3003.13, D_U3002.5
digital_core::/LED/LED_25: D_J3003.14, D_U3002.6
digital_core::/LED/LED_26: D_J3003.15, D_U3002.7
digital_core::/LED/LED_27: D_J3003.16, D_U3002.8
digital_core::/LED/LED_28: D_J3003.17, D_U3002.9
digital_core::/LED/LED_29: D_J3003.18, D_U3002.10
digital_core::/LED/LED_30: D_J3003.19, D_U3002.11
digital_core::/LED/LED_31: D_J3003.20, D_U3002.12
digital_core::/LED/LED_32: D_J3003.21, D_U3002.13
digital_core::/LED/LED_33: D_J3003.22, D_U3002.14
digital_core::/LED/LED_34: D_J3003.23, D_U3002.15
digital_core::/LED/LED_35: D_J3003.24, D_U3002.16
digital_core::/LED/LED_36: D_J3002.24, D_U3002.17
digital_core::/LED/LED_37: D_J3002.23, D_U3002.18
digital_core::/LED/LED_38: D_J3002.22, D_U3002.19
digital_core::/LED/LED_39: D_J3002.21, D_U3002.20
digital_core::/LED/LED_40: D_J3002.20, D_U3002.21
digital_core::/LED/LED_41: D_J3002.19, D_U3002.22
digital_core::/LED/LED_42: D_J3002.18, D_U3002.23
digital_core::/LED/LED_43: D_J3002.17, D_U3002.24
digital_core::/LED/LED_44: D_J3002.16, D_U3002.25
digital_core::/LED/LED_45: D_J3002.15, D_U3002.26
digital_core::/LED/LED_46: D_J3002.14, D_U3002.27
digital_core::/LED/LED_47: D_J3002.13, D_U3002.28
digital_core::/LED/LED_48: D_J3005.1, D_U3003.5
digital_core::/LED/LED_49: D_J3005.2, D_U3003.6
digital_core::/LED/LED_50: D_J3005.3, D_U3003.7
digital_core::/LED/LED_51: D_J3005.4, D_U3003.8
digital_core::/LED/LED_52: D_J3005.5, D_U3003.9
digital_core::/LED/LED_53: D_J3005.6, D_U3003.10
digital_core::/LED/LED_54: D_J3005.7, D_U3003.11
digital_core::/LED/LED_55: D_J3005.8, D_U3003.12
digital_core::/LED/LED_56: D_J3005.9, D_U3003.13
digital_core::/LED/LED_57: D_J3005.10, D_U3003.14
digital_core::/LED/LED_58: D_J3005.11, D_U3003.15
digital_core::/LED/LED_59: D_J3005.12, D_U3003.16
digital_core::/LED/LED_60: D_J3004.12, D_U3003.17
digital_core::/LED/LED_61: D_J3004.11, D_U3003.18
digital_core::/LED/LED_62: D_J3004.10, D_U3003.19
digital_core::/LED/LED_63: D_J3004.9, D_U3003.20
digital_core::/LED/LED_64: D_J3004.8, D_U3003.21
digital_core::/LED/LED_65: D_J3004.7, D_U3003.22
digital_core::/LED/LED_66: D_J3004.6, D_U3003.23
digital_core::/LED/LED_67: D_J3004.5, D_U3003.24
digital_core::/LED/LED_68: D_J3004.4, D_U3003.25
digital_core::/LED/LED_69: D_J3004.3, D_U3003.26
digital_core::/LED/LED_70: D_J3004.2, D_U3003.27
digital_core::/LED/LED_71: D_J3004.1, D_U3003.28
digital_core::/LED/LED_72: D_J3005.13, D_U3004.5
digital_core::/LED/LED_73: D_J3005.14, D_U3004.6
digital_core::/LED/LED_74: D_J3005.15, D_U3004.7
digital_core::/LED/LED_75: D_J3005.16, D_U3004.8
digital_core::/LED/LED_76: D_J3005.17, D_U3004.9
digital_core::/LED/LED_77: D_J3005.18, D_U3004.10
digital_core::/LED/LED_78: D_J3005.19, D_U3004.11
digital_core::/LED/LED_79: D_J3005.20, D_U3004.12
digital_core::/LED/LED_80: D_J3005.21, D_U3004.13
digital_core::/LED/LED_81: D_J3005.22, D_U3004.14
digital_core::/LED/LED_82: D_J3005.23, D_U3004.15
digital_core::/LED/LED_83: D_J3005.24, D_U3004.16
digital_core::/LED/LED_84: D_J3004.24, D_U3004.17
digital_core::/LED/LED_85: D_J3004.23, D_U3004.18
digital_core::/LED/LED_86: D_J3004.22, D_U3004.19
digital_core::/LED/LED_87: D_J3004.21, D_U3004.20
digital_core::/LED/LED_88: D_J3004.20, D_U3004.21
digital_core::/LED/LED_89: D_J3004.19, D_U3004.22
digital_core::/LED/LED_90: D_J3004.18, D_U3004.23
digital_core::/LED/LED_91: D_J3004.17, D_U3004.24
digital_core::/LED/LED_92: D_J3004.16, D_U3004.25
digital_core::/LED/LED_93: D_J3004.15, D_U3004.26
digital_core::/LED/LED_94: D_J3004.14, D_U3004.27
digital_core::/LED/LED_95: D_J3004.13, D_U3004.28
digital_core::/LED/OE_N: D_Q3001.3, D_R3005.1, D_U3005.22
digital_core::/LED/PG_3V3: D_Q3001.1, D_R3006.1, D_R3008.1, D_U3006.1
digital_core::/LED/PG_5V: D_Q3002.1, D_R3007.1, D_R3009.1, D_U3007.1
digital_core::/LED/SERIAL_0: D_U3001.29, D_U3002.4
digital_core::/LED/SERIAL_1: D_U3002.29, D_U3003.4
digital_core::/LED/SERIAL_2: D_U3003.29, D_U3004.4
digital_core::/PROCESSOR/ADC_DATA: D_J1005.4, D_U1001.32
digital_core::/PROCESSOR/ARMED: D_J1003.5, D_R1005.1, D_U1001.37
digital_core::/PROCESSOR/BCLK: D_J1005.2, D_U1001.35
digital_core::/PROCESSOR/DAC_DATA: D_J1005.5, D_R1014.2
digital_core::/PROCESSOR/DAC_DATA_SRC: D_R1014.1, D_U1001.33
digital_core::/PROCESSOR/GAIN_REQ: D_J1003.4, D_R1004.1, D_U1001.10
digital_core::/PROCESSOR/HEARTBEAT: D_J1003.2, D_U1001.14
digital_core::/PROCESSOR/LED_BLANK_SRC: D_R1013.1, D_U1001.15
digital_core::/PROCESSOR/LED_MOSI_SRC: D_R1012.1, D_U1001.11
digital_core::/PROCESSOR/LED_SCK_SRC: D_R1011.1, D_U1001.9
digital_core::/PROCESSOR/LED_XLAT_SRC: D_R1010.1, D_U1001.8
digital_core::/PROCESSOR/MCU_PERMIT: D_J1003.3, D_R1003.1, D_U1001.36
digital_core::/PROCESSOR/POT_ADC_00: D_C1011.1, D_R1031.2, D_R1041.1, D_U1001.22
digital_core::/PROCESSOR/POT_ADC_01: D_C1012.1, D_R1032.2, D_R1042.1, D_U1001.23
digital_core::/PROCESSOR/POT_ADC_02: D_C1013.1, D_R1033.2, D_R1043.1, D_U1001.24
digital_core::/PROCESSOR/POT_ADC_03: D_C1014.1, D_R1034.2, D_R1044.1, D_U1001.25
digital_core::/PROCESSOR/POT_ADC_04: D_C1015.1, D_R1035.2, D_R1045.1, D_U1001.26
digital_core::/PROCESSOR/POT_ADC_05: D_C1016.1, D_R1036.2, D_R1046.1, D_U1001.27
digital_core::/PROCESSOR/POT_ADC_06: D_C1017.1, D_R1037.2, D_R1047.1, D_U1001.28
digital_core::/PROCESSOR/POT_ADC_07: D_C1018.1, D_R1038.2, D_R1048.1, D_U1001.29
digital_core::/PROCESSOR/POT_ADC_08: D_C1019.1, D_R1039.2, D_R1049.1, D_U1001.30
digital_core::/PROCESSOR/POT_ADC_09: D_C1020.1, D_R1040.2, D_R1050.1, D_U1001.31
digital_core::/PROCESSOR/POT_RAW_00: D_J1020.2, D_R1031.1
digital_core::/PROCESSOR/POT_RAW_01: D_J1021.2, D_R1032.1
digital_core::/PROCESSOR/POT_RAW_02: D_J1022.2, D_R1033.1
digital_core::/PROCESSOR/POT_RAW_03: D_J1023.2, D_R1034.1
digital_core::/PROCESSOR/POT_RAW_04: D_J1024.2, D_R1035.1
digital_core::/PROCESSOR/POT_RAW_05: D_J1025.2, D_R1036.1
digital_core::/PROCESSOR/POT_RAW_06: D_J1026.2, D_R1037.1
digital_core::/PROCESSOR/POT_RAW_07: D_J1027.2, D_R1038.1
digital_core::/PROCESSOR/POT_RAW_08: D_J1028.2, D_R1039.1
digital_core::/PROCESSOR/POT_RAW_09: D_J1029.2, D_R1040.1
digital_core::/PROCESSOR/SDMMC_CLK: D_J1012.8, D_R1020.2
digital_core::/PROCESSOR/SDMMC_CLK_SRC: D_R1020.1, D_U1001.7
digital_core::/PROCESSOR/SDMMC_CMD: D_J1012.7, D_R1019.2
digital_core::/PROCESSOR/SDMMC_CMD_SRC: D_R1019.1, D_U1001.6
digital_core::/PROCESSOR/SDMMC_D0: D_J1012.3, D_R1015.2
digital_core::/PROCESSOR/SDMMC_D0_SRC: D_R1015.1, D_U1001.5
digital_core::/PROCESSOR/SDMMC_D1: D_J1012.4, D_R1016.2
digital_core::/PROCESSOR/SDMMC_D1_SRC: D_R1016.1, D_U1001.4
digital_core::/PROCESSOR/SDMMC_D2: D_J1012.5, D_R1017.2
digital_core::/PROCESSOR/SDMMC_D2_SRC: D_R1017.1, D_U1001.3
digital_core::/PROCESSOR/SDMMC_D3: D_J1012.6, D_R1018.2
digital_core::/PROCESSOR/SDMMC_D3_SRC: D_R1018.1, D_U1001.2
digital_core::/PROCESSOR/SEED_VIN: D_C1001.1, D_C1002.1, D_R1001.2, D_U1001.39
digital_core::/PROCESSOR/V3V3_ANALOG: D_C1003.1, D_C1004.1, D_J1020.3, D_J1021.3, D_J1022.3, D_J1023.3, D_J1024.3, D_J1025.3, D_J1026.3, D_J1027.3, D_J1028.3, D_J1029.3, D_U1001.21
digital_core::/PROCESSOR/WS: D_J1005.3, D_U1001.34
digital_core::AGND: D_C1001.2, D_C1002.2, D_C1003.2, D_C1004.2, D_C1005.2, D_C1006.2, D_C1011.2, D_C1012.2, D_C1013.2, D_C1014.2, D_C1015.2, D_C1016.2, D_C1017.2, D_C1018.2, D_C1019.2, D_C1020.2, D_C2001.2, D_C2002.2, D_C2003.2, D_C2004.2, D_C3001.2, D_C3002.2, D_C3003.2, D_C3004.2, D_C3005.2, D_C3006.2, D_C3007.2, D_C3008.2, D_C3009.2, D_C3010.2, D_C3011.2, D_C3012.2, D_C3013.2, D_C3014.2, D_J1001.2, D_J1003.1, D_J1004.1, D_J1005.1, D_J1006.1, D_J1007.1, D_J1008.1, D_J1009.1, D_J1010.1, D_J1012.1, D_J1013.2, D_J1014.2, D_J1015.2, D_J1020.1, D_J1021.1, D_J1022.1, D_J1023.1, D_J1024.1, D_J1025.1, D_J1026.1, D_J1027.1, D_J1028.1, D_J1029.1, D_J2001.15, D_J2001.16, D_J2002.15, D_J2002.16, D_J2003.1, D_Q3002.2, D_R1003.2, D_R1004.2, D_R1005.2, D_R1006.2, D_R1041.2, D_R1042.2, D_R1043.2, D_R1044.2, D_R1045.2, D_R1046.2, D_R1047.2, D_R1048.2, D_R1049.2, D_R1050.2, D_R2001.2, D_R2002.2, D_R2003.2, D_R3001.2, D_R3002.2, D_R3003.2, D_R3004.2, D_R3008.2, D_R3009.2, D_R3012.2, D_R3013.2, D_R3014.2, D_R3019.2, D_R3020.2, D_R3021.2, D_U1001.20, D_U1001.40, D_U2001.10, D_U2001.15, D_U2001.16, D_U2001.17, D_U2002.10, D_U2002.16, D_U2002.17, D_U2003.10, D_U2003.15, D_U2003.17, D_U3001.1, D_U3001.33, D_U3002.1, D_U3002.33, D_U3003.1, D_U3003.33, D_U3004.1, D_U3004.33, D_U3005.7, D_U3005.8, D_U3005.9, D_U3005.10, D_U3005.11, D_U3005.12, D_U3005.13, D_U3006.2, D_U3007.2
digital_core::ANALOG_OK: D_J1004.4, D_J1006.6, D_R2002.1, D_U2003.23
digital_core::BYPASS_SENSE: D_J1003.6, D_J1004.3, D_U2003.22
digital_core::CODEC_RUN: D_J1006.5, D_R1006.1, D_R2001.1, D_U1001.1, D_U2001.18, D_U2002.18, D_U2003.18
digital_core::INPUT_READY: D_J1004.5, D_J1007.2, D_R2003.1, D_U2003.24
digital_core::LED_BLANK: D_R1002.1, D_R1013.2, D_R3010.1, D_U3005.6
digital_core::LED_MOSI: D_R1012.2, D_R3019.1, D_U3005.3
digital_core::LED_SCK: D_R1011.2, D_R3020.1, D_U3005.4
digital_core::LED_XLAT: D_R1010.2, D_R3021.1, D_U3005.5
digital_core::MODE_SEND_RETURN: D_J1004.2, D_J1008.2, D_U2003.21
digital_core::SCL: D_J1006.3, D_J1009.3, D_J1010.3, D_U1001.12, D_U2001.12, D_U2002.12, D_U2003.12
digital_core::SDA: D_J1006.4, D_J1009.4, D_J1010.4, D_U1001.13, D_U2001.13, D_U2002.13, D_U2003.13
digital_core::V3V3_IO: D_C1005.1, D_C1006.1, D_C2001.1, D_C2002.1, D_C2003.1, D_C2004.1, D_C3009.1, D_C3011.1, D_J1006.2, D_J1009.2, D_J1010.2, D_J1012.2, D_R1002.2, D_R3005.2, D_R3006.2, D_R3010.2, D_U1001.38, D_U2001.9, D_U2002.9, D_U2002.15, D_U2003.9, D_U2003.16, D_U3005.1, D_U3005.2, D_U3006.3, D_U3006.5, D_U3006.6
